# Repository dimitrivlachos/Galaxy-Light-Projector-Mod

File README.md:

# Galaxy Light Projector Mod
Modification of a consumer night-light projector, converting it into a smart device with a custom PCB, powered by an ESP-32.

## Features
- Alexa integration
- Complex color patterns
- Improved brightness
- Better circuit protection

## Custom PCB

### KiCad Render (Rev. 1.1)
<table>
  <tr>
    <td>Front</td>
  </tr>
    <td></td>
  </tr>
  <tr>
    <td>Back</td>
  </tr>
  <tr>
    <td></td>
 </table>

 ### Fabrication Render (Rev. 1.1)
  <table>
    <tr>
      <td>Front</td>
    </tr>
      <td></td>
    </tr>
    <tr>
      <td>Back</td>
    </tr>
    <tr>
      <td></td>
    </table>

### Printed Circuit Board (Rev. 1.0)
<table>
  <tr>
    <td>Bare</td>
  </tr>
    <td></td>
  <tr>
    <td>Assembled Front</td>
  </tr>
    <td></td>
  </tr>
  <tr>
    <td>Assembled Back</td>
  </tr>
  <tr>
    <td></td>
 </table>

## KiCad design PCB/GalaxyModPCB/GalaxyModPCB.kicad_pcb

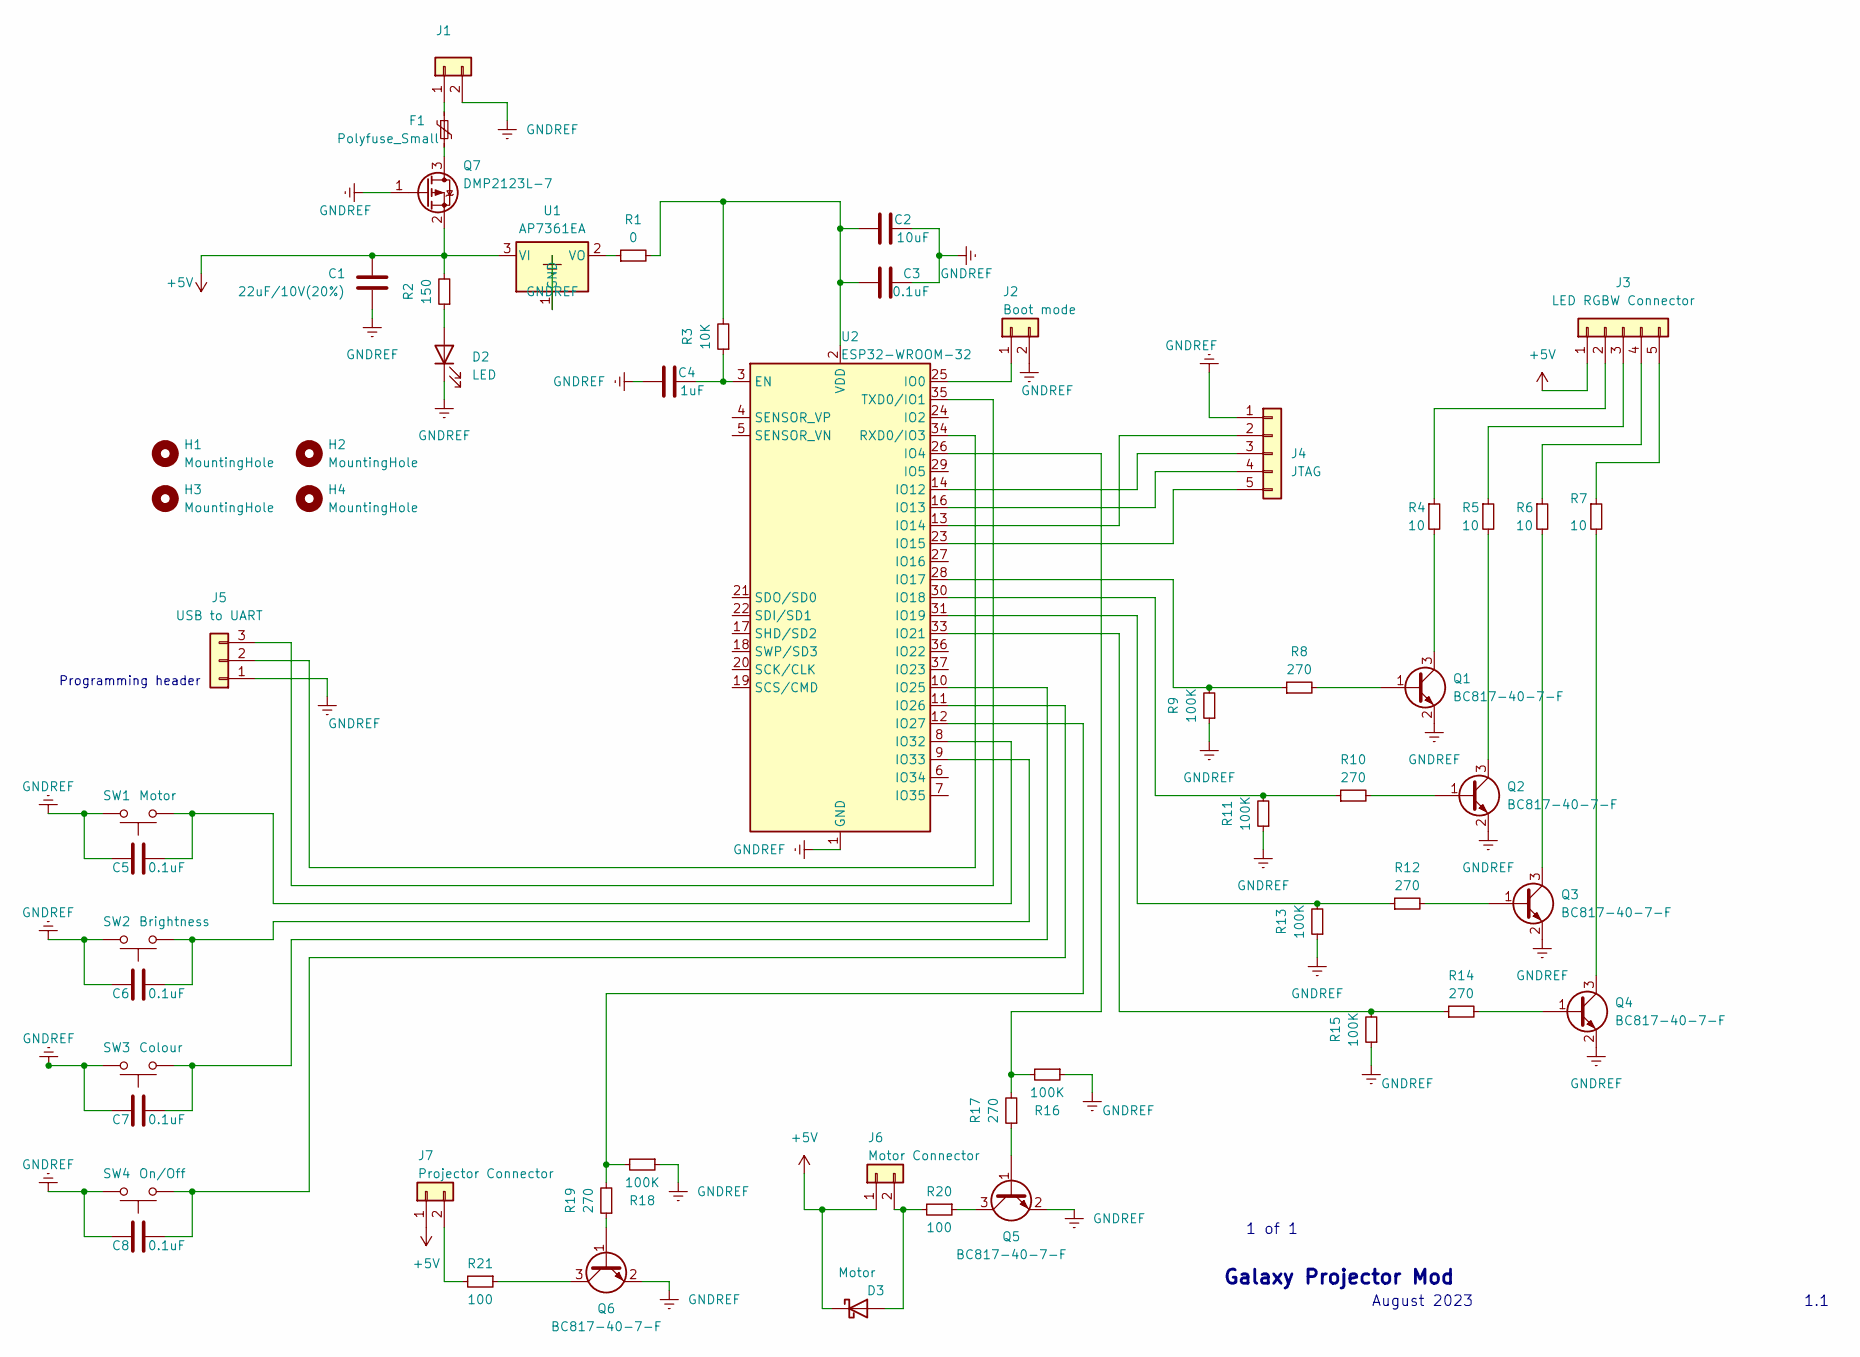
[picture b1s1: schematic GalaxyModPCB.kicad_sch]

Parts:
C1: 22uF/10V(20%); C_0805_2012Metric
C2: 10uF; C_0805_2012Metric
C3, C5, C6, C7, C8: 0.1uF; C_0805_2012Metric
C4: 1uF; C_0805_2012Metric
D2: LED; LED_0603_1608Metric_Pad1.05x0.95mm_HandSolder
D3: Motor; D_SMA_Handsoldering JLCPCB
F1: Polyfuse_Small; R_0805_2012Metric_Pad1.20x1.40mm_HandSolder
H1, H2: MountingHole; MountingHole_2mm Galaxy Small
H3, H4: MountingHole; 2.5mm Big Hole
J1: Power Header; PinHeader_1x02_P2.54mm_Vertical
J2: Boot mode; Triangle Jumper
J3: LED RGBW Connector; PinHeader_1x05_P2.54mm_Vertical
J4: JTAG; JTAG Connector
J5: USB to UART; UART Connector
J6: Motor Connector; PinHeader_1x02_P2.54mm_Vertical
J7: Projector Connector; PinHeader_1x02_P2.54mm_Vertical
Q1, Q2, Q3, Q4, Q5, Q6: BC817-40-7-F; SOT-23
Q7: DMP2123L-7; SOT-23
R1: 0; R_0805_2012Metric_Pad1.20x1.40mm_HandSolder
R2: 150; R_0805_2012Metric_Pad1.20x1.40mm_HandSolder
R3: 10K; R_0805_2012Metric_Pad1.20x1.40mm_HandSolder
R4, R5, R6, R7: 10; R_2512_6332Metric_Pad1.40x3.35mm_HandSolder
R8, R10, R12, R14, R17, R19: 270; R_0805_2012Metric_Pad1.20x1.40mm_HandSolder
R9, R11, R13, R15, R16, R18: 100K; R_0805_2012Metric_Pad1.20x1.40mm_HandSolder
R20, R21: 100; R_0805_2012Metric_Pad1.20x1.40mm_HandSolder
SW1: Motor; Galaxy Switch
SW2: Brightness; Galaxy Switch
SW3: Colour; Galaxy Switch
SW4: On/Off; Galaxy Switch
U1: AP7361EA; SOT-223-3_TabPin2
U2: ESP32-WROOM-32; ESP32-WROOM-32 No Thermal

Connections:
+5V: C1.1, D3.1 (K), J3.1, J6.1, J7.1, Q7.2 (S), R2.2, U1.3 (VI)
GNDREF: C1.2, C2.2, C3.2, C4.1, C5.2, C6.2, C7.2, C8.2, D2.1 (K), J1.2, J2.2, J4.1, J5.1, Q1.2 (E), Q2.2 (E), Q3.2 (E), Q4.2 (E), Q5.2 (E), Q6.2 (E), Q7.1 (G), R9.1, R11.1, R13.1, R15.1, R16.1, R18.1, SW1.2, SW2.2, SW3.2, SW4.2, U1.1 (GND), U2.1 (GND), U2.15 (GND), U2.38 (GND), U2.39 (GND)
unnamed: D2.2 (A), R2.1
unnamed: D3.2 (A), J6.2, R20.2
unnamed: F1.1, J1.1
unnamed: J2.1, U2.25 (IO0)
unnamed: J3.2, R4.1
unnamed: J3.3, R5.1
unnamed: J3.4, R6.1
unnamed: J3.5, R7.1
unnamed: J4.2, U2.13 (IO14)
unnamed: J4.3, U2.14 (IO12)
unnamed: J4.4, U2.16 (IO13)
unnamed: J4.5, U2.23 (IO15)
unnamed: J5.2, U2.34 (RXD0/IO3)
unnamed: J5.3, U2.35 (TXD0/IO1)
unnamed: J7.2, R21.2
unnamed: Q1.1 (B), R8.2
unnamed: Q1.3 (C), R4.2
unnamed: Q2.1 (B), R10.2
unnamed: Q2.3 (C), R5.2
unnamed: Q3.1 (B), R12.2
unnamed: Q3.3 (C), R6.2
unnamed: Q4.1 (B), R14.2
unnamed: Q4.3 (C), R7.2
unnamed: Q5.1 (B), R17.1
unnamed: Q5.3 (C), R20.1
unnamed: Q6.1 (B), R19.1
unnamed: Q6.3 (C), R21.1
unnamed: F1.2, Q7.3 (D)
unnamed: R1.1, U1.2 (VO)
unnamed: C4.2, R3.1, U2.3 (EN)
unnamed: R16.2, R17.2, U2.26 (IO4)
unnamed: R8.1, R9.2, U2.28 (IO17)
unnamed: R10.1, R11.2, U2.30 (IO18)
unnamed: R12.1, R13.2, U2.31 (IO19)
unnamed: R14.1, R15.2, U2.33 (IO21)
unnamed: C7.1, SW3.1, U2.10 (IO25)
unnamed: C8.1, SW4.1, U2.11 (IO26)
unnamed: R18.2, R19.2, U2.12 (IO27)
unnamed: C5.1, SW1.1, U2.8 (IO32)
unnamed: C6.1, SW2.1, U2.9 (IO33)
unnamed: C2.1, C3.1, R1.2, R3.2, U2.2 (VDD)

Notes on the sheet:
1.1
Galaxy Projector Mod
1 of 1
August 2023
Programming header

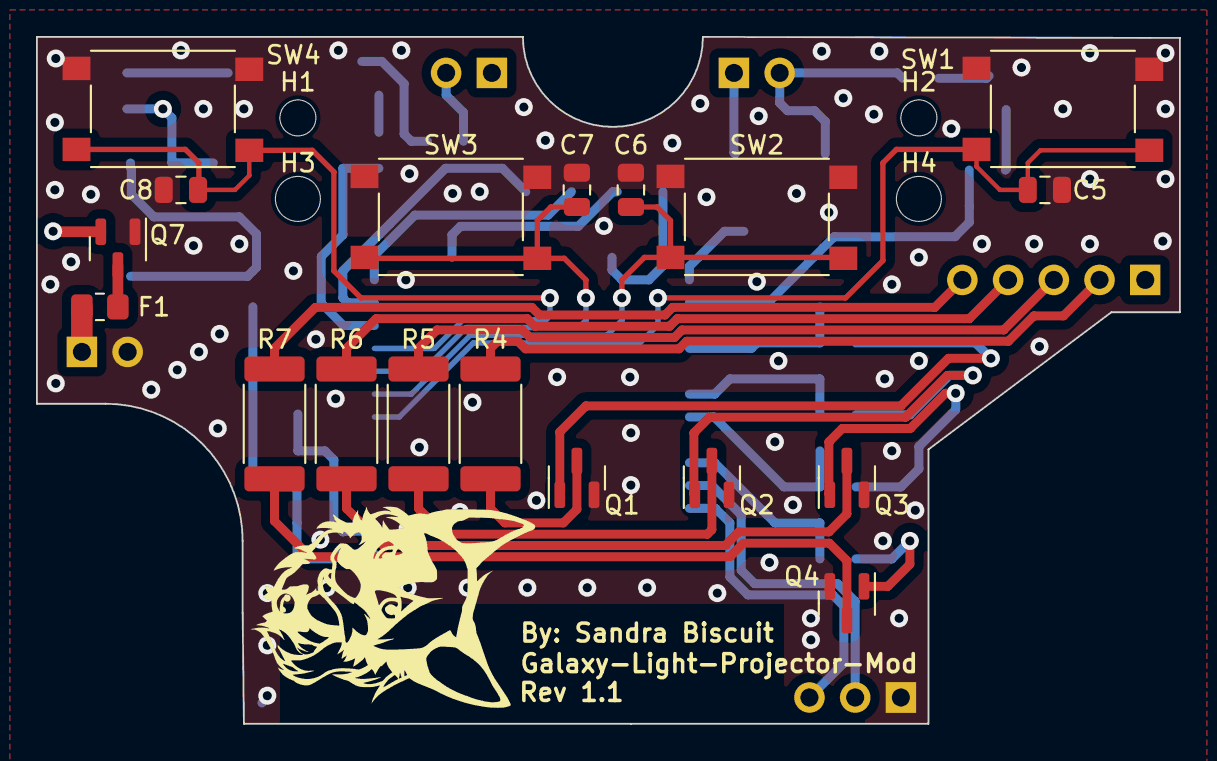
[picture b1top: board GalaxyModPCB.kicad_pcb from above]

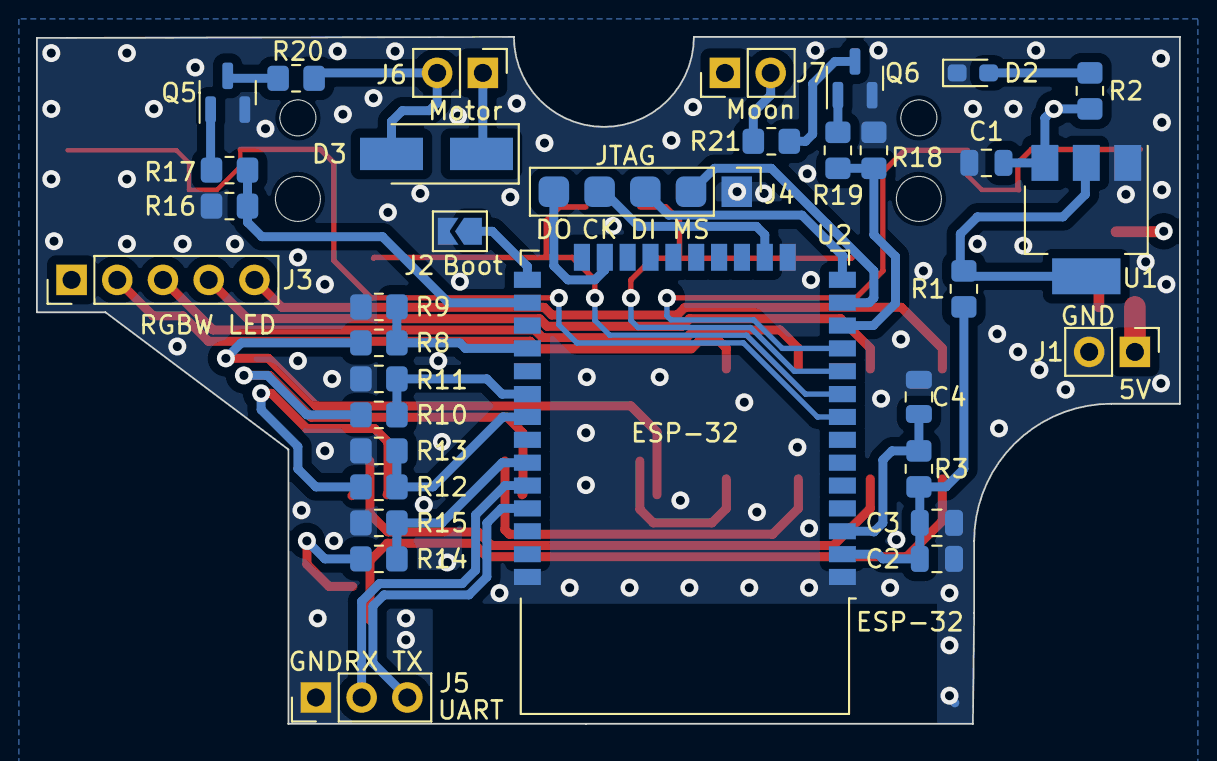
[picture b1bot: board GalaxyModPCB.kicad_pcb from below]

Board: 4 copper layers, 63.5 x 38.2 mm, 56 parts (34 on the bottom side), 43 nets.

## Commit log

2023-07-25 Basic blinker with OTA
2023-07-31 Created empty PCB sketch
    Created a KiCad project for the design of the PCB for this project
2023-08-01 Began work on basic schematic
2023-08-01 Placed correct ESP board
2023-08-01 Added voltage regulator circuitry
2023-08-01 Changed to esp32
2023-08-01 Neatened wiring
2023-08-01 Changed to connector
2023-08-02 Large revision
2023-08-02 First draft drawn
2023-08-02 Labelled and named
2023-08-02 Added switches
2023-08-02 Added debugging header
2023-08-02 Fixed annotations
2023-08-02 Annotation changes
2023-08-02 Fixed connector footprints
2023-08-02 Added power connector
2023-08-02 Assigned footprints
2023-08-02 Laid out basic PCB arrangement
2023-08-03 Copied original PCB edge cuts
2023-08-03 Added boot mode header
2023-08-03 Fixed pin header footprints
2023-08-03 Updated footprints on PCB
2023-08-03 Updated switch footprints
2023-08-03 Adjusted board
2023-08-03 Aligned switches
2023-08-03 Added board cutout
2023-08-03 Fixed power header size
2023-08-03 Fixed RVP diode
2023-08-03 Arranged power supply
2023-08-03 Wired power circuitry
2023-08-03 Fixed small tracing issue
2023-08-03 Fixed traces
2023-08-03 Connect switch peripherals
2023-08-03 Fixed motor diode footprint
2023-08-03 Fixed sketch trace connections
2023-08-03 Fixed RVP of sketch
2023-08-03 Connected power circuitry
2023-08-03 Added cutout for antenna
2023-08-03 Connected power to esp32
2023-08-03 Traces
2023-08-03 Fixed SW1 connection
2023-08-03 Powered switches
2023-08-03 Wired up LED header
2023-08-03 Began work on projector LED
2023-08-03 Corrected projector LED power
2023-08-03 Updated projector LED requirements
2023-08-03 Corrected component sides
2023-08-03 Wired up projector
2023-08-03 Wired first LED
2023-08-03 LED circuitry arrangement draft
2023-08-03 Updated LED resistors
    Changed from 4 small to 1 large resistor per LED. This doubles the heat dissipation and reduces footprint
2023-08-03 Connected data signals
2023-08-03 Improved traces
2023-08-03 Neatened traces
2023-08-03 Improved pin selection
2023-08-03 Attached buttons
2023-08-03 Connected all but ground
2023-08-04 Added mounting holes to sketch
2023-08-04 Fixed mounting holes
2023-08-04 Placed mounting holes
2023-08-04 Accounted for mounting holes
2023-08-04 Connected transistors
2023-08-04 Neatened tracks
2023-08-04 Added ground fill
2023-08-04 Connected ground planes
2023-08-04 Removed old traces
2023-08-04 Added JLCPCB custom rules
2023-08-04 Adjusted board thickness
2023-08-04 Part shift
2023-08-04 Changed headers to pins
2023-08-04 Adjusted footprints
2023-08-04 Labelled power header
2023-08-04 Updated power nets
2023-08-05 Part separation for reconfiguration
2023-08-05 Fixed transistor direction
2023-08-05 Updated transistor connections
2023-08-05 Placed fill zones
2023-08-05 Filled power domains
2023-08-05 Updated 0 ohm resistor
2023-08-05 Updated diode footprints
2023-08-05 Updated annotations
2023-08-05 Arranged power circuitry
2023-08-05 Arranged and connected power
2023-08-05 Rearranged componenets
2023-08-05 Roughly placed most components
2023-08-06 Arranged parts for tracing
2023-08-06 Updated fill layers
2023-08-06 Initial power traces drawn
2023-08-06 Close save data
2023-08-08 Part re-organisation
2023-08-08 Improved LED vias
2023-08-08 Fixed multiple vias
2023-08-08 Connected LED transistors
2023-08-08 Arranged and connected peripheral circuits
2023-08-08 Neatened and connected vias
2023-08-08 Rearranged and wired inputs
2023-08-08 EN wired
2023-08-08 Re-connected planes
2023-08-09 Re-wired switches
2023-08-09 Added documentation
2023-08-09 Removed unnecessary 3.3 net
2023-08-09 Imported changes into PCB
2023-08-09 Added KiCad backups to gitignore
2023-08-09 Actually removed backup folder from repo
2023-08-09 Re-annotated schematic
2023-08-09 Updated PCB with new annotations
2023-08-09 Removed unnecessary resistors
2023-08-09 Adapted new buttons
2023-08-09 Removed 3.3v domain
2023-08-09 Minor tweaks to position
2023-08-09 Fixed most violations and errors
2023-08-09 Fixed Diode silkscreen issue
2023-08-09 Resolved courtyard overlap
2023-08-09 Adjusted labels
2023-08-09 Capacitor label adjustment
2023-08-09 Changed boot jumper to pad
2023-08-09 Changed power header to proper size
2023-08-09 Re-filled solid planes
2023-08-09 Updated USB header to pads
2023-08-09 Replaced RGB header with 2.5mm
2023-08-09 Re-filled planes
2023-08-09 Updated motor header
2023-08-09 Re-filled
2023-08-10 Updated projector header
2023-08-10 Added some documentation
2023-08-10 Labelled RX TX
2023-08-10 Improved labels
2023-08-10 Misc closing information
2023-08-10 Updated REAMDE with examples
2023-08-10 Change mosfet to bjt
2023-08-10 Imported BJTs into PCB
2023-08-10 Major LED placement change
2023-08-10 Connected all but islands
2023-08-10 Connected all nets
2023-08-10 Changed outer layer fill to solid
2023-08-10 Updated silkscreen
2023-08-10 Connected islands
2023-08-10 Updated schematic with BJTs
2023-08-10 Replaced BJTs
2023-08-12 Added resistor to motor
2023-08-12 Added motor resistor
2023-08-12 Save
2023-08-13 Close data
2023-08-13 Updated resistors for motor control
2023-08-14 icy layout suggestions
2023-08-14 added gnd to jtag connector -> routing up next
2023-08-14 Updated Kicad and LED
2023-08-14 Created custom footprints
2023-08-14 Updated footprints in schematic
2023-08-14 Flipped JTAG header
2023-08-14 Updated footprints
2023-08-14 Added logo
2023-08-14 Closed
2023-08-14 Updated LED to correct size
2023-08-15 Updated datasheets
2023-08-15 Added KiCad ignores
2023-08-15 Removed ignored files
2023-08-15 Updated labels and traces
2023-08-15 Removed dangerous vias
2023-08-15 Created Gerber files for fabrication
2023-08-15 Updated examples
2023-08-15 Created blank project
    Created a blank PlatformIO project for the code base.
2023-08-15 Created basic blinker
2023-08-16 Basic pin test program
2023-08-16 Implemented AsyncOTA
2023-08-16 pio changes
2023-08-16 Generated Fab examples
2023-08-16 Updated LED definitions
    Updated definitions to correspond with their correct LED on the board
2023-08-16 Added simple state
2023-08-17 Added DNS settings
2023-08-17 Added boot messages
2023-08-17 Annotated init code
2023-08-17 Built basic test program
2023-08-17 Removed DNS settings
2023-08-17 Created test multitask program
2023-08-17 Improved info
2023-08-17 Improved syntax
2023-08-18 Example fix
2023-08-18 Updated README examples
2023-08-18 Refactored tasks
2023-08-18 Implemented switch logic
2023-08-18 Build
2023-08-19 Added state handling
2023-08-19 Small formatting improvement
2023-08-19 Removed loop()
2023-08-19 Grouped state handling
2023-08-19 Implemented all original functions
2023-08-19 Improved variable name
2023-08-19 Refactored incorrect names
2023-08-19 Fixed incorrect numbering
2023-08-19 Added offline functionality
2023-08-19 Fixed offline operation
2023-08-19 Added all documentation
2023-08-19 Fix to state change conditions
2023-08-20 Implemented functional websocket web interface
2023-08-20 State updates on webpage
2023-08-20 Visual enhancement
2023-08-22 Updated part references
2023-08-22 Fixed right-angle trace connection
2023-08-22 Updated revision number
2023-08-27 Removed button emulation function
    Commented the logic that prevents the other switches from cycling states when powered off. This is a good design in the original but with a device that is always on, even when the lights are off, it 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
2023-08-27 Added revision number
    Added revision number to example images
2023-09-08 Added Polyfuze
2023-09-08 Fixed transistor
2023-09-08 Changed back to triangle jumper
2023-09-08 Changed revision number
2023-09-08 Updated PCB
    Incorporated fuze and fixed transistor footprints
2023-09-08 Small positioning fixes
2023-09-08 Improved power to plane
2023-09-08 Close
2023-09-09 Replaced RVP diode with PMOS
    Replaced RVP diode with PMOS fet in sketch for reduced power loss
2023-09-10 Replaced RVP Diode with PMOS
2023-09-11 Correccted PMOS
2023-09-11 Greatly improved part placement
2023-09-11 Updated JTAG connector
2023-09-11 Updated UART Connector
2023-09-12 Changed label
2023-09-12 Fixed reference mismatch
2023-09-12 Fixed labels
2023-09-12 Updated README with new examples
2023-09-14 Updated properties
2023-09-14 Added basic implementation of a switch and led
2023-09-16 Updated Switch class
2023-09-16 Optimised Switch class
2023-09-16 Refactored loop names for clarity
2023-09-16 Created generic FSM for object states
2023-09-16 Updated states
2023-09-16 Refactored for FSM usage
2023-09-16 Fixed switch pin assignment
2023-09-16 Fixed power switch name
2023-09-16 Updated switch
2023-09-16 Implemented onStateChange websocket update
2023-09-17 Fixed legacy calls
2023-09-17 Added action-state map
2023-09-17 Test interface changes
2023-09-19 Setting change
2023-09-19 Added init for actions
2023-09-19 Tweaked look of slider
2023-09-22 Created generic fsm object
2023-09-22 Created pwm device object
2023-09-22 Created rgbw object
2023-09-22 Created state object
2023-09-22 Created switch object
2023-09-22 Refactored to using new objects and header files
2023-09-22 Added copy constructor
2023-09-22 Debugged
2023-09-22 Defined upload speed
2023-09-22 Corrected switch pins
2023-09-22 Cleaned up main
2023-09-23 Added set and custom modes to website
2023-09-23 Updated outbound websocket communication
2023-09-23 Fixed send colour bug
2023-09-23 Added max connection attempts
2023-09-23 Individual custom functions
2023-09-23 Max connection attempts error message added
2023-09-23 Corrected annoying American spelling
2023-09-28 Pushing non-functional code
2023-09-28 Pin definition fix
2023-09-28 Shifted label
2023-09-28 Generated fabrication files for Rev 1,1
2023-09-28 Examples updated
2023-09-28 Fixed pin definitions
2023-09-29 Updated fabrication renders
